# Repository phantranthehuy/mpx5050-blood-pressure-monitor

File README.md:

# 🩺 Digital Oscillometric Blood Pressure Monitor

> An academic research project focused on designing and developing a digital blood pressure monitor using the **MPX5050** pressure sensor and the **Oscillometric Method**.

## 📖 Table of Contents
- [About the Project](#about-the-project)
- [Key Features](#key-features)
- [Team Members](#team-members)
- [System Architecture](#system-architecture)
- [Technology Stack](#technology-stack)
- [Repository Structure](#repository-structure)
- [Getting Started](#getting-started)
- [License](#license)

## 🔬 About the Project
This repository contains the hardware schematics, embedded C firmware, and signal processing algorithms for an automated blood pressure monitor. 

The system operates based on the **Oscillometric Method**. It extracts tiny pressure oscillations (AC component) superimposed on the static cuff pressure (DC component) during the deflation phase. By analyzing the envelope of these oscillations, the system calculates the Mean Arterial Pressure (MAP), Systolic Pressure (SYS), Diastolic Pressure (DIA), and Heart Rate (BPM).

## ✨ Key Features
- **Automated Cuff Control:** Smooth inflation and linear deflation using a DC pump and a solenoid valve.
- **High-Precision Sensing:** Utilizes the MPX5050DP sensor with a custom Analog Front-End (AFE) for signal amplification and band-pass filtering (0.5Hz - 5Hz).
- **DSP Algorithms:** Implements digital filtering and envelope detection algorithms to accurately identify blood pressure parameters.
- **User Interface:** Real-time pressure monitoring and final result display via an LCD/OLED screen.

## 👥 Team Members
| Name | Role | Responsibilities |
| :--- | :--- | :--- |
| **Phan Tran The Huy** | **Project Manager & Hardware Lead** | Overall project management, Altium/KiCad schematic & PCB design, and hardware integration. |
| **Tran Nhat Ly** | **Mechanical & UI/UX Engineer** | 3D enclosure design, mechanical assembly, component sourcing, and UI programming. |
| **Nguyen Huy Hoang** | **DSP Algorithm & Research Lead** | Signal processing research (Kalman/FIR filters), data analysis, and technical documentation. |
| **Cao Hoang Tung** | **Embedded Software Engineer** | STM32 C programming, Pump/Valve driver implementation, and translating MATLAB/Python algorithms into embedded C. |

## 📐 System Architecture

The core of the system relies on capturing and separating the pressure signals:

## 🛠 Technology Stack
- **Microcontroller:** STM32 Series
- **Firmware:** C (STM32 HAL, CMake) trong `firmware/stm32-hal-cmake/`; tùy chọn C/C++ Arduino (STM32duino) trong `firmware/stm32-arduino-pio/`.
- **Development Environment:** VS Code with STM32CubeIDE Extension (HAL) hoặc VS Code + PlatformIO (Arduino, `firmware/stm32-arduino-pio/`).
- **Hardware Design:** Altium Designer / KiCad
- **Simulation Tools:** LTSpice (Analog filtering), Python/MATLAB (Algorithm verification)

## 📂 Repository Structure
```text
📦 mpx5050-blood-pressure-monitor
 ┣ 📂 Algorithms      # Python/MATLAB scripts for algorithm simulation & signal filtering
 ┣ 📂 Docs            # Datasheets, academic papers, and technical reports
 ┣ 📂 firmware        # stm32-hal-cmake (CMake+HAL) + stm32-arduino-pio (PlatformIO Arduino)
 ┣ 📂 Hardware        # Schematics, PCB layouts, and Bill of Materials (BOM)
 ┣ 📂 Mechanical      # 3D models and CAD files for the device enclosure
 ┣ 📜 .gitignore      # Ignored files for STM32, VS Code, and EDA tools
 ┣ 📜 LICENSE         # MIT License
 ┗ 📜 README.md       # Project documentation
```

## 🚀 Getting Started

### Prerequisites
- **VS Code** installed with the `C/C++` and `STM32 VS Code Extension`.
- **STM32CubeMX** (for modifying microcontroller pinouts/clocks).
- **Git** for version control.

### Installation & Build
1. **Clone the repository:**
   ```bash
   git clone https://github.com/your-username/mpx5050-blood-pressure-monitor.git
   ```
2. **Open the firmware (HAL / CMake):**
   Open the `firmware/stm32-hal-cmake` directory in VS Code (CMake + STM32 HAL).
3. **Optional — Arduino framework (same MCU):**
   Open `firmware/stm32-arduino-pio` in VS Code with the PlatformIO extension, or run `pio run` from that folder (see `firmware/stm32-arduino-pio/README.md`).
4. **Compile:**
   Press `Ctrl + Shift + B` (or use the STM32 extension build button) to compile the C code and generate the `.elf` / `.hex` files.
5. **Flash to MCU:**
   Connect your ST-Link debugger and click `Run > Start Debugging` (F5) to flash the firmware onto the STM32.

## ⚖️ License
This project is licensed under the **MIT License** - see the [LICENSE](LICENSE) file for details. Designed for academic and research purposes.

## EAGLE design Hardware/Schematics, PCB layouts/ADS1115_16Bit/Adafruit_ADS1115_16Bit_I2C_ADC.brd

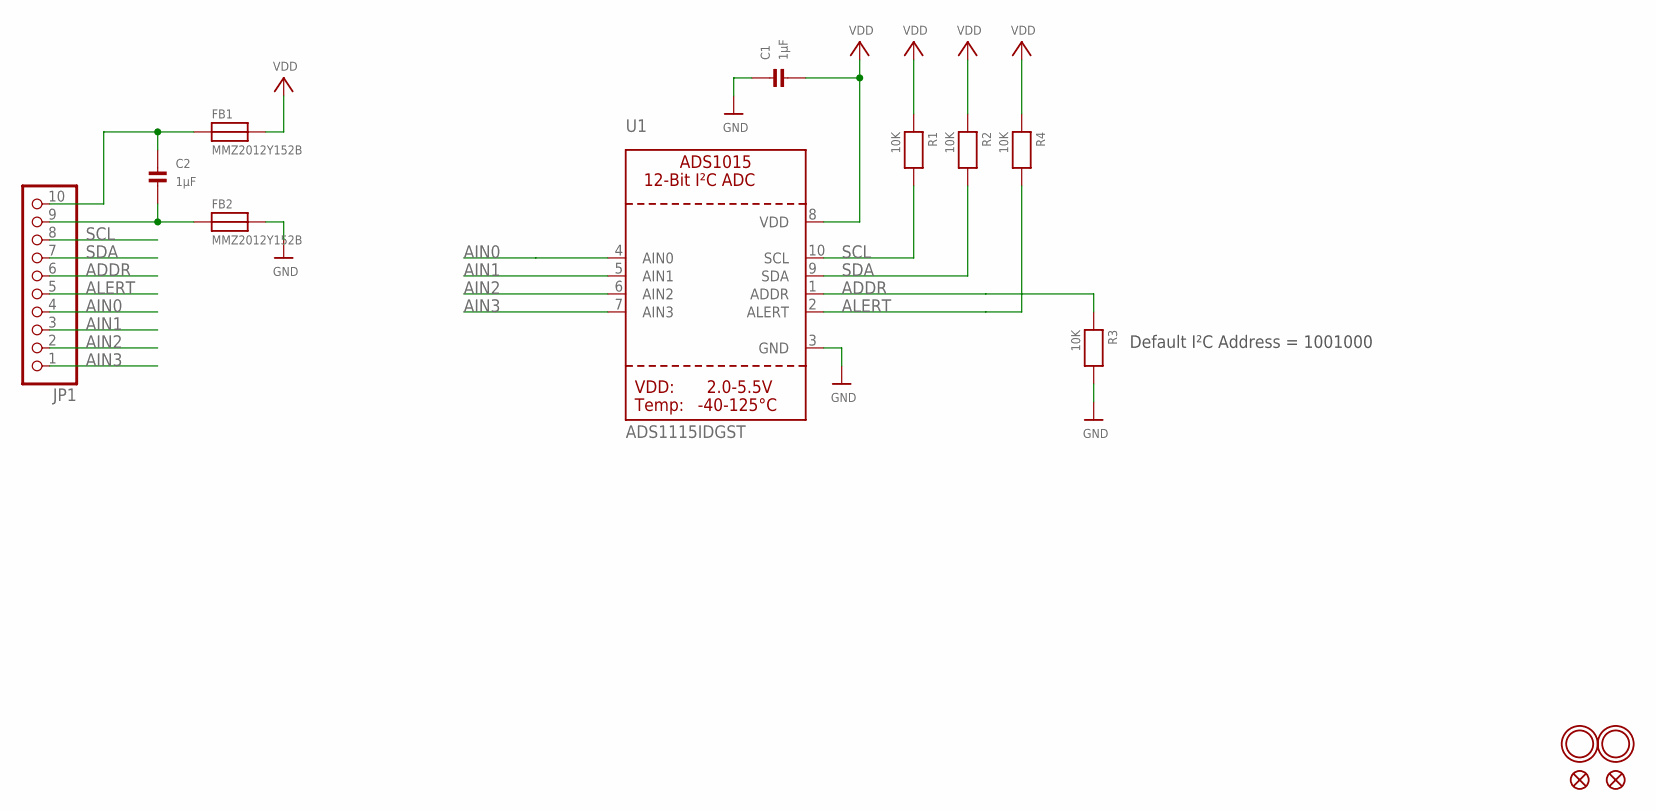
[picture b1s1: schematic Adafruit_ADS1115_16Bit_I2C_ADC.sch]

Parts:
C1, C2: 1µF; 0805
FB1, FB2: MMZ2012Y152B; 0805
FID1, FID2: FIDUCIAL""; FIDUCIAL_1MM
JP1: HEADER-1X1070MIL; 1X10_ROUND70
R1, R2, R3, R4: 10K; 0805
U1: ADS1115IDGST; MSOP10
U$13, U$14: MOUNTINGHOLE2.5; MOUNTINGHOLE_2.5_PLATED

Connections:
ADDR: JP1.6, R3.1, U1.1 (ADDR)
AIN0: JP1.4, U1.4 (AIN0)
AIN1: JP1.3, U1.5 (AIN1)
AIN2: JP1.2, U1.6 (AIN2)
AIN3: JP1.1, U1.7 (AIN3)
ALERT: JP1.5, R4.2, U1.2 (ALERT)
GND: C1.1, FB2.2, R3.2, U1.3 (GND)
unnamed: C2.1, FB1.1, JP1.10
unnamed: C2.2, FB2.1, JP1.9
SCL: JP1.8, R1.2, U1.10 (SCL)
SDA: JP1.7, R2.2, U1.9 (SDA)
VDD: C1.2, FB1.2, R1.1, R2.1, R4.1, U1.8 (VDD)

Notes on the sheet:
Default I²C Address = 1001000

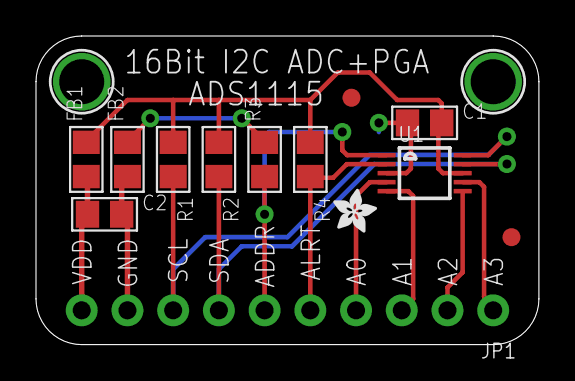
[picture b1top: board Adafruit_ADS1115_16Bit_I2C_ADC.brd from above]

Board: 2 copper layers, 27.9 x 17.1 mm, 16 parts (1 on the bottom side), 12 nets.

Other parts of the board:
U$15: ADAFRUIT_TEXT_20MM
U$16: ADAFRUIT_2.5MM

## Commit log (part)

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2026-03-20 Create .gitignore for multiple development environments
    Added a comprehensive .gitignore file for C/C++, STM32, Altium Designer, KiCad, LTSpice, and general OS files.
2026-03-20 Revise README for project overview and setup
    Updated README to include detailed project information, features, team members, and setup instructions.
2026-03-20 Create CONTRIBUTING.md for team guidelines
    Added a contributing guide for the team to manage GitHub usage effectively.
2026-03-20 Enhance CONTRIBUTING.md with clearer GitHub usage steps
    Updated instructions for using GitHub Desktop and committing changes.
2026-03-20 Update CONTRIBUTING.md with new guidelines
2026-03-20 Change repository URL in CONTRIBUTING.md
    Updated the repository URL in the CONTRIBUTING.md file.
2026-03-21 Tạo file word thử
2026-03-21 Firmware
2026-03-21 tạo folder
2026-03-21 test nha chat
2026-03-22 Tìm linh kiện upload
2026-04-03 Thêm schematic.pdf
2026-04-03 Revise GitHub usage guidelines for team
    Updated the guidelines for using GitHub, including rules for branches, daily workflow, and pull requests.
2026-05-12 debug(uart): include ADC counts in sample stream
2026-05-12 hw(pins): remap buttons/PWM and move 100Hz tick to TIM3
    - Buttons → PA11/PA8/PB12, PWM bơm/van → PA0/PA1 (TIM2_CH1/CH2).
    - Đổi tick 100 Hz từ TIM2 sang TIM3 vì TIM2 nay phục vụ analogWrite()
    cho PWM 1 kHz trên PA0/PA1. Thứ tự setup: analogWriteFrequency() trước,
    rồi mới HardwareTimer(TIM3) để tránh reconfig nhầm timer của tick.
2026-05-12 feat(fsm): pump soft-start and slope cap to mitigate brownout
    Khi motor bơm khởi động kéo dòng inrush gấp 5-10 lần dòng chạy,
    nguồn không đủ gồng sẽ kéo VCC sụt < 3V → STM32 brownout-reset.
    Thêm 3 giới hạn trong bp_fsm.c để giảm di/dt và đỉnh dòng:
    - IDLE→INFLATE: kick khởi đầu giảm từ 15% xuống PUMP_PWM_MIN (5%).
    - Soft-start window: trong PUMP_SOFTSTART_MS (500ms) đầu sau khi rời
    IDLE, kẹp pump_pwm ≤ PUMP_SOFTSTART_CAP_PCT (30%).
2026-05-12 debug(stream): include FSM state, PWM and buttons in S,... line
    Dòng S,... mở rộng thành
    S,seq,t_ms,p_mmHg,rc,counts,fsm,pump%,valve%,btnSPH
    để mỗi tick đều thấy trạng thái FSM, PWM bơm/van và 3 nút (đã đảo
    active-low). Hỗ trợ chẩn đoán hiện tượng "bấm START mà motor không
    chạy" — phân biệt được rơi vào state nào (FAST_DEFLATE do STOP stuck,
    ERROR do I2C, hay đang INFLATE nhưng PWM không lên do nguồn).
